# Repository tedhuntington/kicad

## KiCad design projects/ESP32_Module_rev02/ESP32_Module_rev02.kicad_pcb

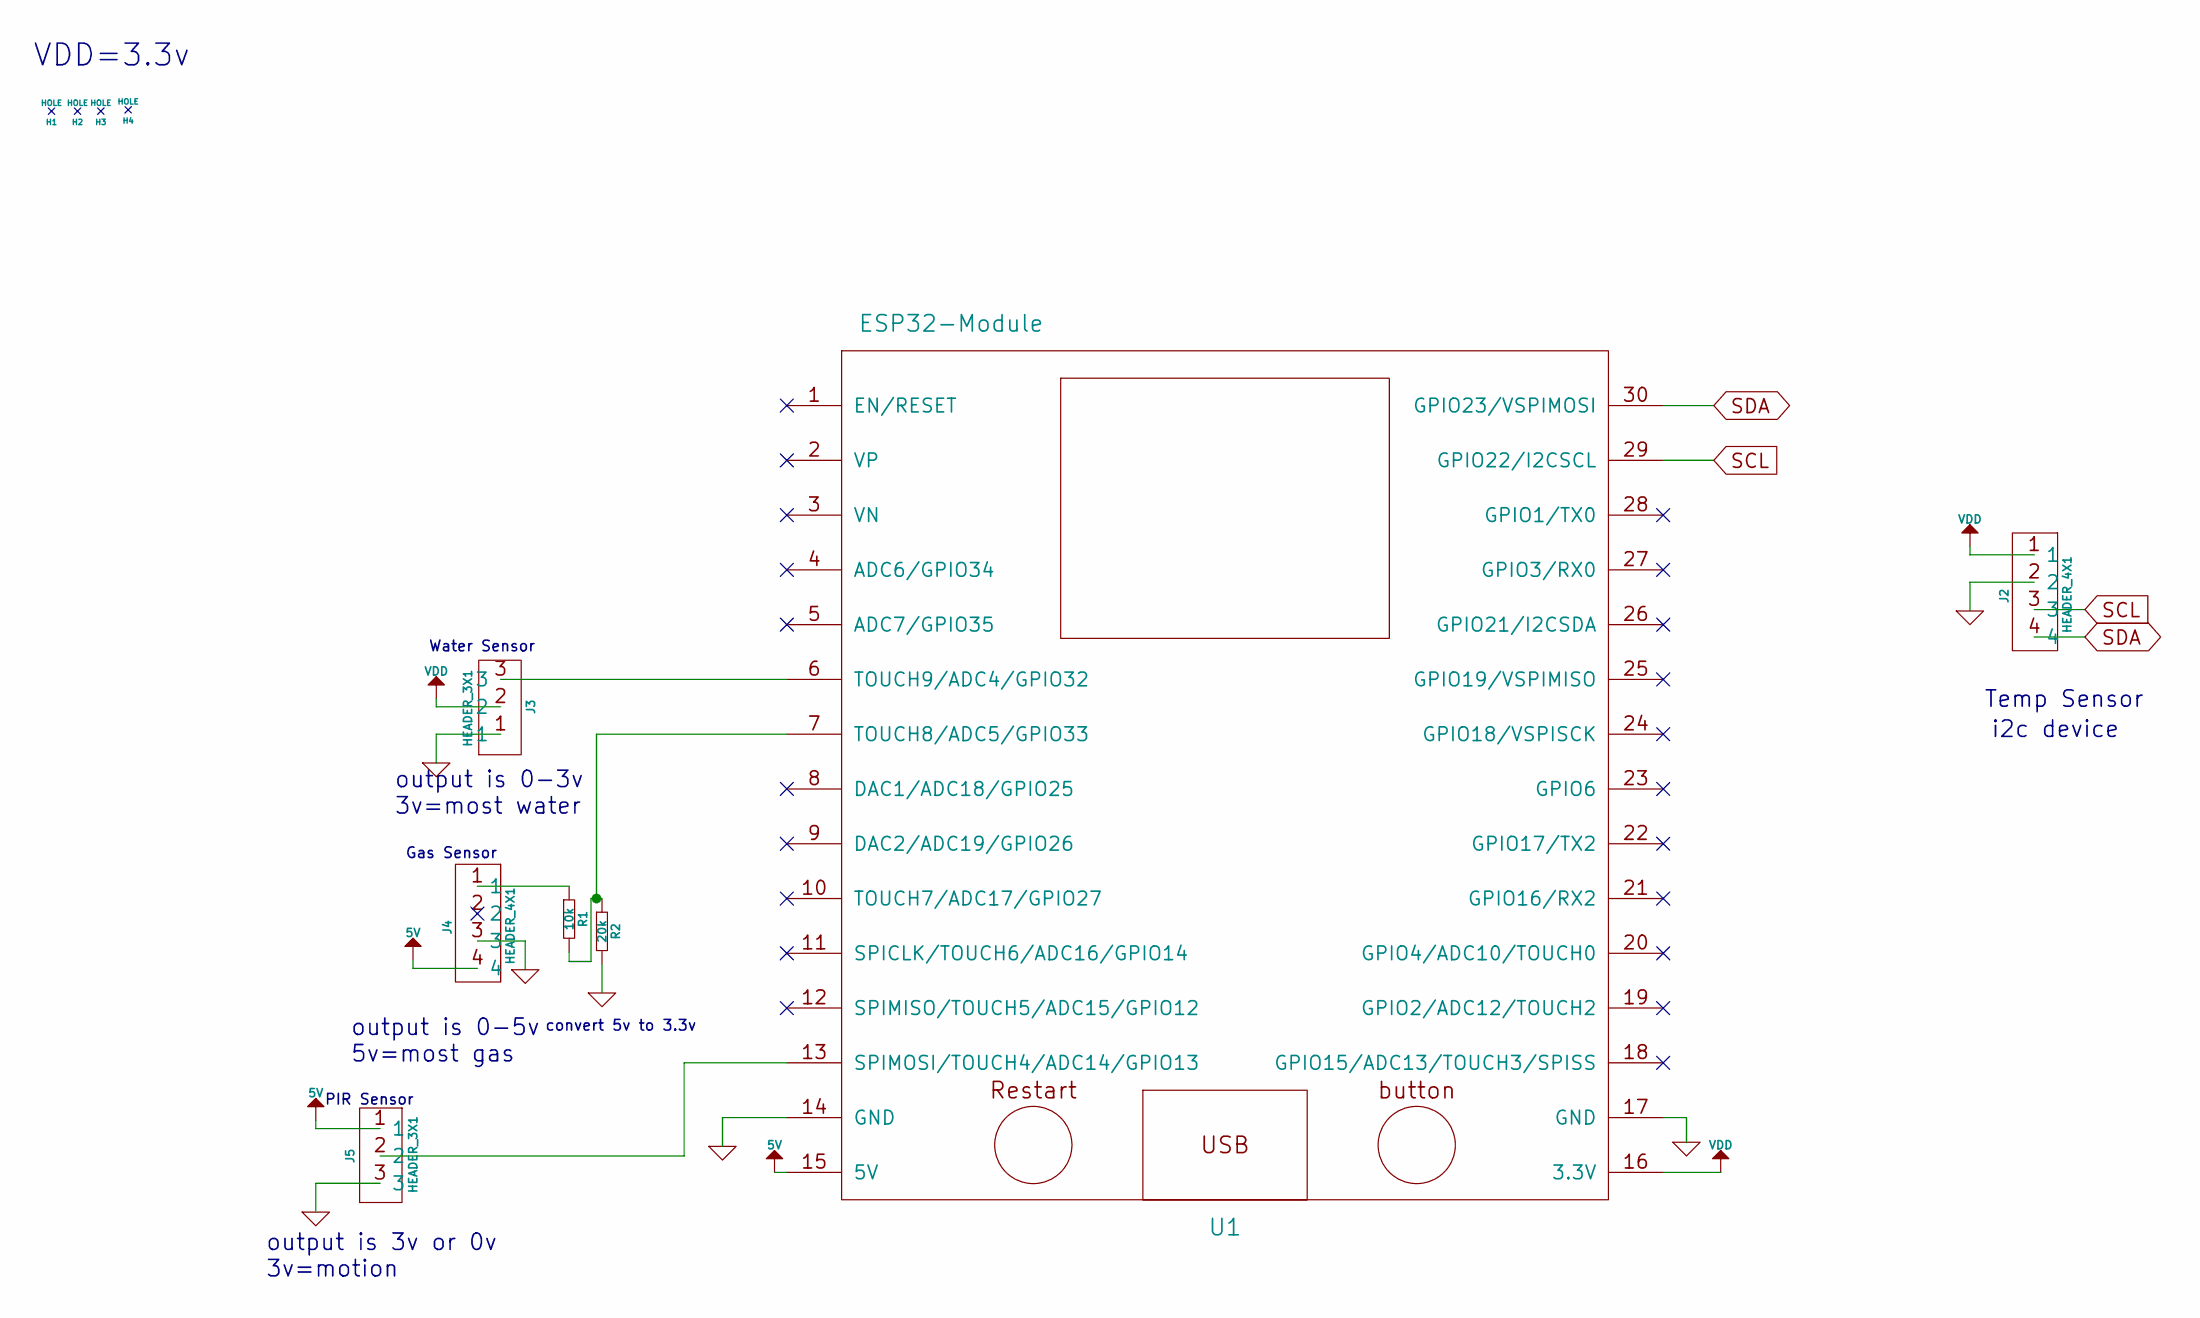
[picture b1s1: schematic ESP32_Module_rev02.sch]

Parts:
H1, H2, H3, H4: HOLE; TED_Hole_3mm
J2, J4: HEADER_4X1; TED_HEADER_4x1
J3, J5: HEADER_3X1; TED_HEADER_3x1
R1: 10k; TED_SM0603_R
R2: 20k; TED_SM0603_R
U1: ESP32-Module; TED_ESP32_Module_30pin

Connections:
5V: J4.4, J5.1, U1.15 (5V)
GND: J2.2, J3.1, J4.3, J5.3, R2.2, U1.14 (GND), U1.17 (GND); also elsewhere on the board
unnamed 2: U1.1 (EN/RESET); also elsewhere on the board
unnamed: J3.3, U1.6 (TOUCH9/ADC4/GPIO32)
unnamed: J4.1, R1.1
unnamed: J5.2, U1.13 (SPIMOSI/TOUCH4/ADC14/GPIO13)
unnamed: R1.2, R2.1, U1.7 (TOUCH8/ADC5/GPIO33)
SCL: J2.3, U1.29 (GPIO22/I2CSCL)
SDA: J2.4, U1.30 (GPIO23/VSPIMOSI)
VDD: J2.1, J3.2, U1.16 (3.3V)

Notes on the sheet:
VDD=3.3v
Water Sensor
PIR Sensor
Temp Sensor
output is 3v or 0v 3v=motion
output is 0-3v 3v=most water
i2c device
Gas Sensor
output is 0-5v 5v=most gas
convert 5v to 3.3v

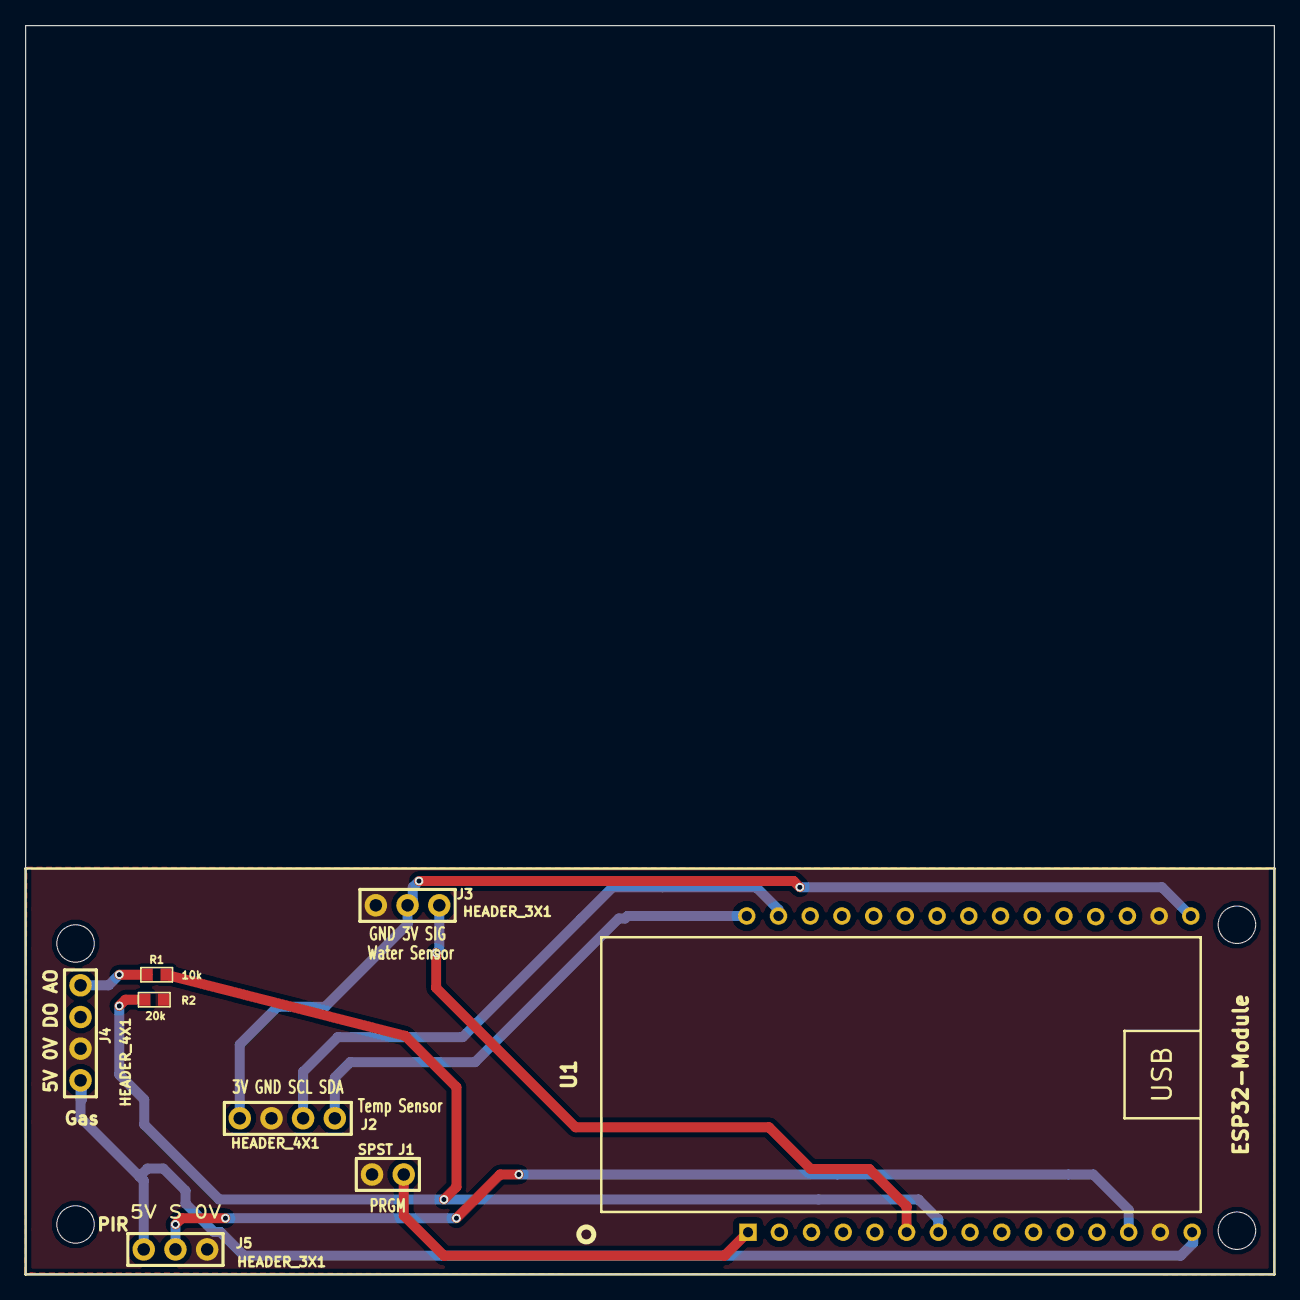
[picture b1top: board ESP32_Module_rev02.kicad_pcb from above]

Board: 2 copper layers, 100.0 x 100.0 mm, 12 parts (0 on the bottom side), 10 nets.

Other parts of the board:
J1: SPST; TED_DIPSWITCH_1

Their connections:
GND: J1.2; also elsewhere on the board
unnamed 2: J1.1; also elsewhere on the board

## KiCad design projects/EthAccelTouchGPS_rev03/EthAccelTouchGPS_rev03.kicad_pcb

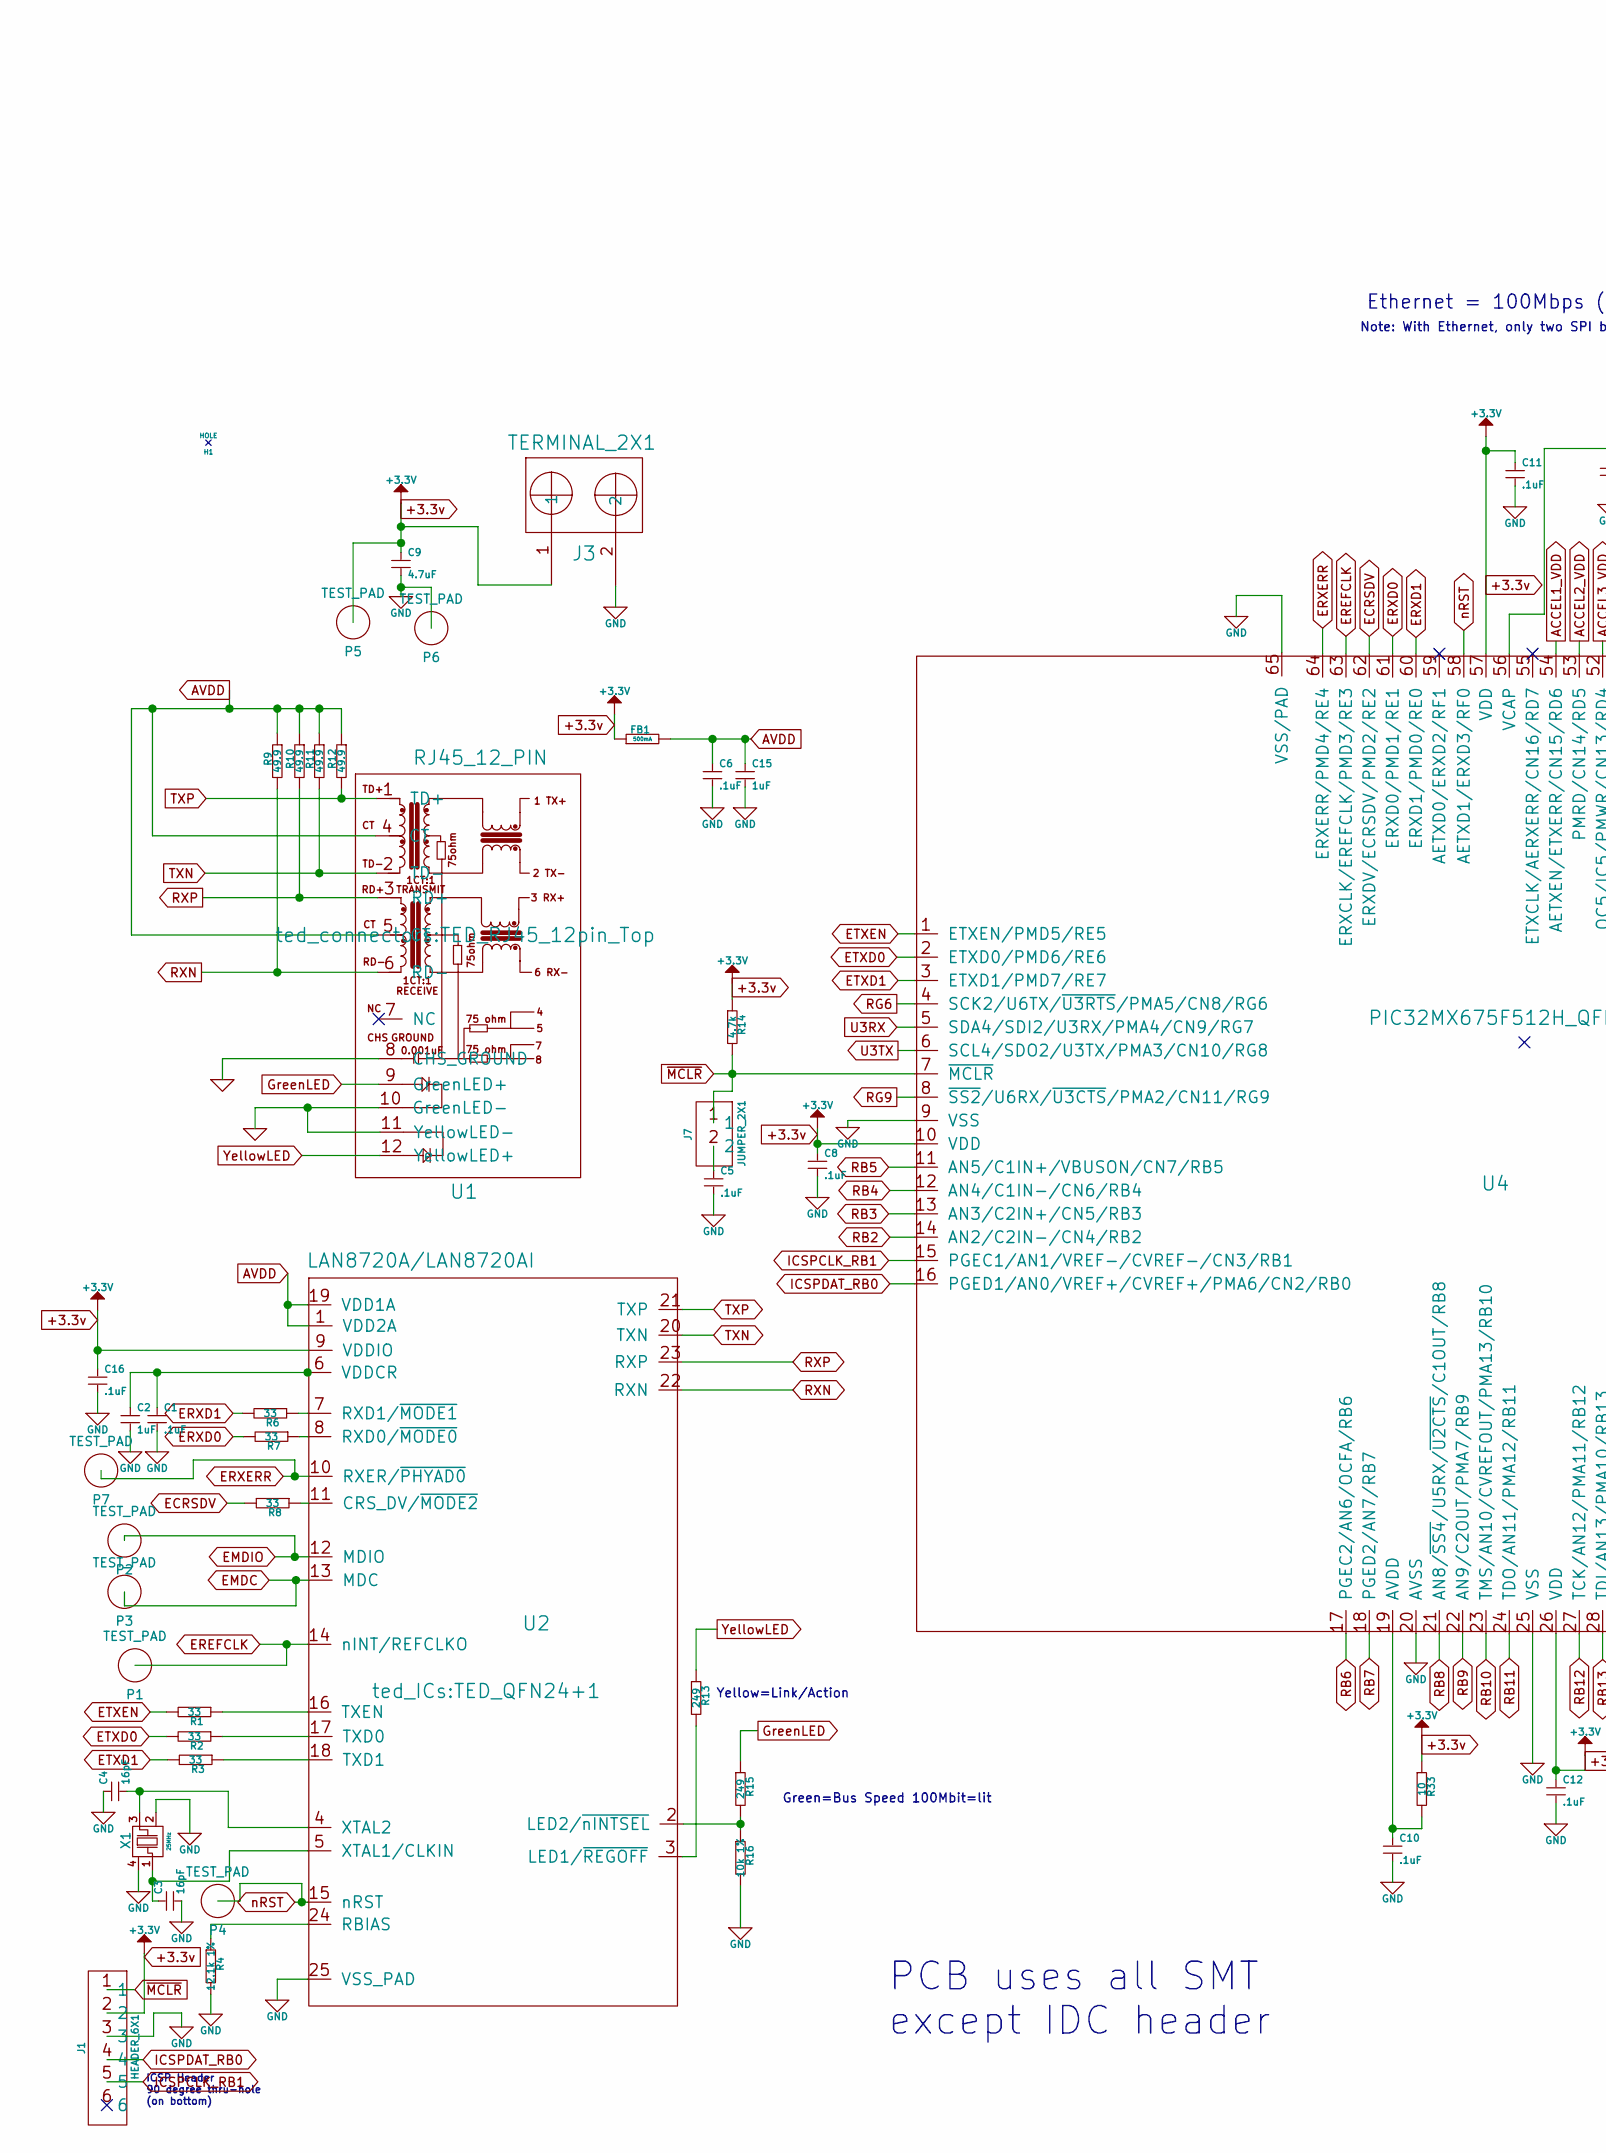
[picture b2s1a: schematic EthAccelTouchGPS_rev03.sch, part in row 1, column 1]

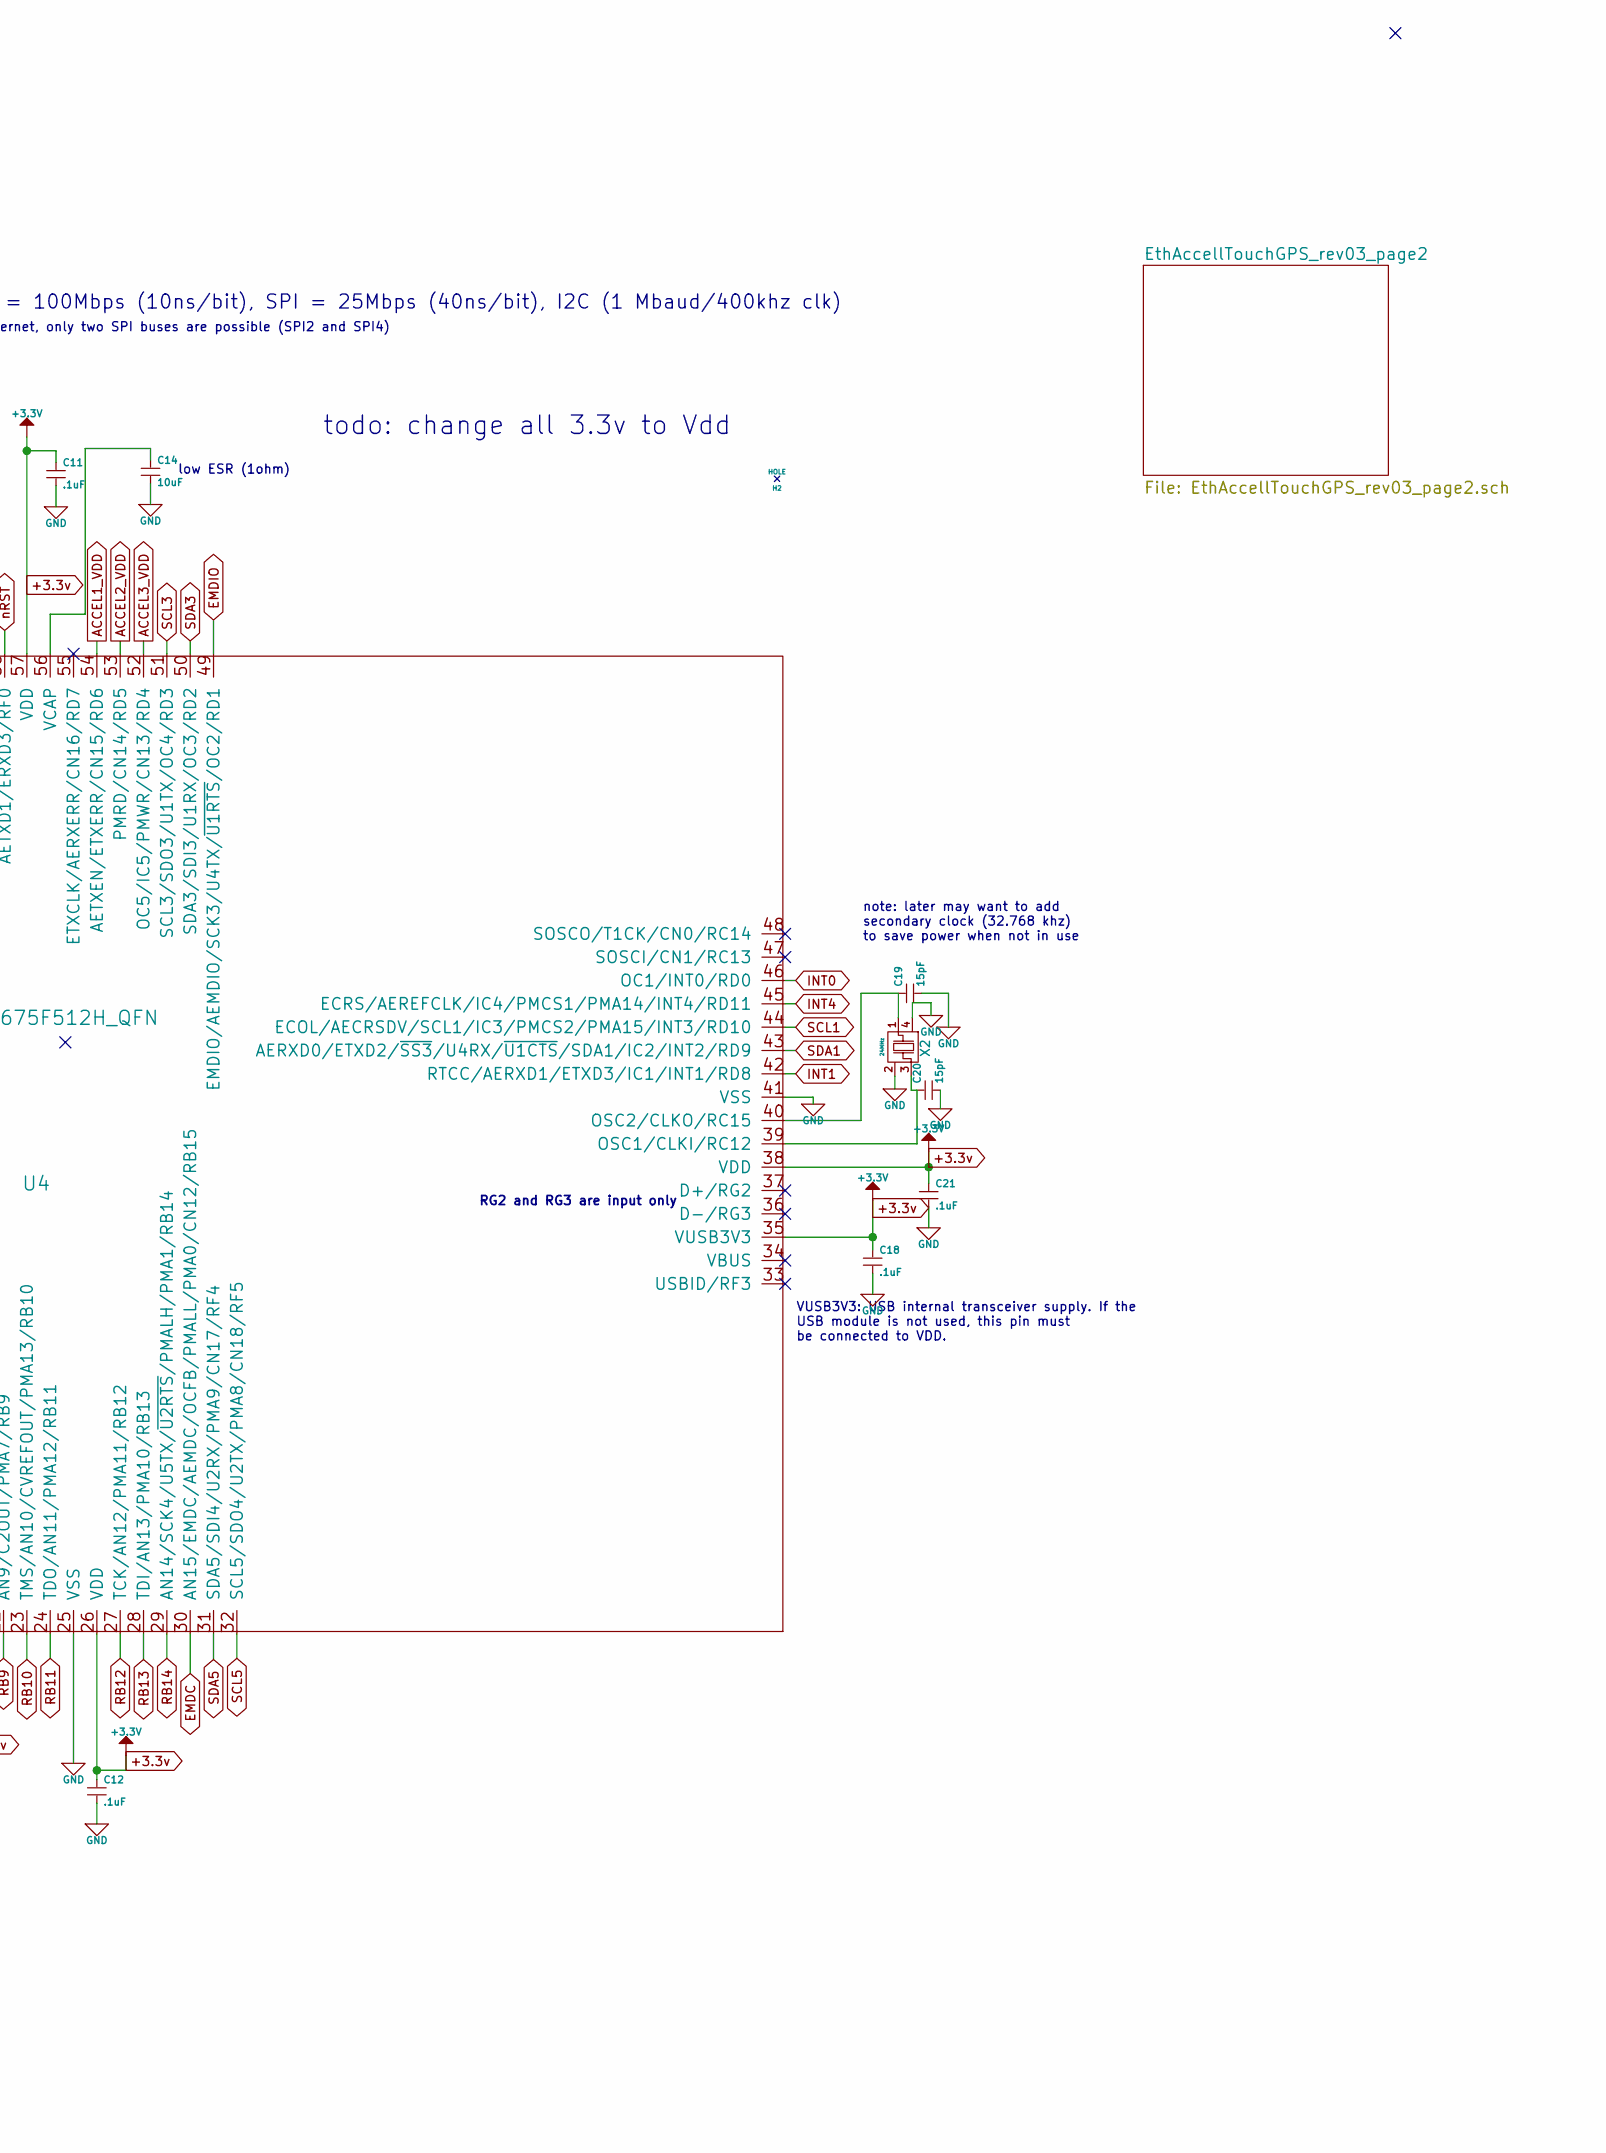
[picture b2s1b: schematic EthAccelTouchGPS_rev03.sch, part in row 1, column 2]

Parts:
C1, C5, C6, C8, C10, C11, C12, C16, C18, C21: .1uF; TED_SM1608_0603_C
C2, C15: 1uF; TED_SM1608_0603_C
C3, C4: 16pF; TED_SM1608_0603_C
C9: 4.7uF; TED_SM1608_0603_C
C14: 10uF; TED_SM2012_0805_C
C19, C20: 15pF; TED_SM1608_0603_C
FB1: 500mA; TED_SM0805_R
H1, H2: HOLE; TED_Hole_3mm
J1: HEADER_6X1; TED_HEADER_6x1
J3: TERMINAL_2X1; TED_TERMINAL_SPRING_2.54MM_2PIN_1989748
J7: JUMPER_2X1; TED_JUMPER_2x1_SMD
P1, P2, P3, P4, P5, P6, P7: TEST_PAD; TED_TEST_PAD
R1, R2, R3, R6, R7, R8: 33; TED_SM0603_R
R4: 12.1k 1%; TED_SM0603_R
R9, R10, R11, R12: 49.9; TED_SM0603_R
R13, R15: 249; TED_SM0603_R
R14: 4.7k; TED_SM0603_R
R16: 10k 1%; TED_SM0603_R
R33: 10; TED_SM0603_R
U1: RJ45_12_PIN; TED_RJ45_12pin_Top
U2: LAN8720A/LAN8720AI; TED_QFN24+1
U4: PIC32MX675F512H_QFN; TED_QFN64+1H
X1: 25MHz; TED_crystal_FA-20H
X2: 24MHz; crystal_TSX3225

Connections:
+3.3v: C8.1, C9.1, C11.1, C12.1, C16.1, C18.1, C21.1, FB1.1, J1.2, J3.1, P5.1, R14.1, R33.1, U2.9 (VDDIO), U4.10 (VDD), U4.26 (VDD), U4.35 (VUSB3V3), U4.38 (VDD), U4.57 (VDD); also elsewhere on the board
ACCEL1_VDD: U4.54 (AETXEN/ETXERR/CN15/RD6); also elsewhere on the board
ACCEL2_VDD: U4.53 (PMRD/CN14/RD5); also elsewhere on the board
ACCEL3_VDD: U4.52 (OC5/IC5/PMWR/CN13/RD4); also elsewhere on the board
AVDD: C6.1, C15.1, FB1.2, R9.1, R10.1, R11.1, R12.1, U1.4 (CT), U1.5 (CT), U2.1 (VDD2A), U2.19 (VDD1A)
ECRSDV: R8.2, U4.62 (ERXDV/ECRSDV/PMD2/RE2)
EMDC: P3.1, U2.13 (MDC), U4.30 (AN15/EMDC/AEMDC/OCFB/PMALL/PMA0/CN12/RB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)
EMDIO: P2.1, U2.12 (MDIO), U4.49 (EMDIO/AEMDIO/SCK3/U4TX/~U1RTS~/OC2/RD1)
EREFCLK: P1.1, U2.14 (nINT/REFCLKO), U4.63 (ERXCLK/EREFCLK/PMD3/RE3)
ERXD0: R7.2, U4.61 (ERXD0/PMD1/RE1)
ERXD1: R6.2, U4.60 (ERXD1/PMD0/RE0)
ERXERR: P7.1, U2.10 (RXER/~PHYAD0~), U4.64 (ERXERR/PMD4/RE4)
ETXD0: R2.2, U4.2 (ETXD0/PMD6/RE6)
ETXD1: R3.2, U4.3 (ETXD1/PMD7/RE7)
ETXEN: R1.2, U4.1 (ETXEN/PMD5/RE5)
GND: C1.2, C2.2, C3.2, C4.1, C5.2, C6.2, C8.2, C9.2, C10.2, C11.2, C12.2, C14.2, C15.2, C16.2, C18.2, C19.2, C20.2, C21.2, J1.3, J3.2, P6.1, R4.2, R16.2, U1.8 (CHS_GROUND), U1.10 (GreenLED-), U1.11 (YellowLED-), U2.25 (VSS_PAD), U4.9 (VSS), U4.20 (AVSS), U4.25 (VSS), U4.41 (VSS), U4.65 (VSS/PAD), X1.2, X1.4, X2.2, X2.4; also elsewhere on the board
GreenLED: R15.1, U1.9 (GreenLED+)
ICSPCLK_RB1: J1.5, U4.15 (PGEC1/AN1/VREF-/CVREF-/CN3/RB1); also elsewhere on the board
ICSPDAT_RB0: J1.4, U4.16 (PGED1/AN0/VREF+/CVREF+/PMA6/CN2/RB0); also elsewhere on the board
INT0: U4.46 (OC1/INT0/RD0); also elsewhere on the board
INT1: U4.42 (RTCC/AERXD1/ETXD3/IC1/INT1/RD8); also elsewhere on the board
INT4: U4.45 (ECRS/AEREFCLK/IC4/PMCS1/PMA14/INT4/RD11); also elsewhere on the board
unnamed: C1.1, C2.1, U2.6 (VDDCR)
unnamed: C3.1, U2.5 (XTAL1/CLKIN), X1.1
unnamed: C4.2, U2.4 (XTAL2), X1.3
unnamed: C5.1, J7.2
unnamed: C10.1, R33.2, U4.19 (AVDD)
unnamed: C14.1, U4.56 (VCAP)
unnamed: C19.1, U4.40 (OSC2/CLKO/RC15), X2.1
unnamed: C20.1, U4.39 (OSC1/CLKI/RC12), X2.3
unnamed: R1.1, U2.16 (TXEN)
unnamed: R2.1, U2.17 (TXD0)
unnamed: R3.1, U2.18 (TXD1)
unnamed: R4.1, U2.24 (RBIAS)
unnamed: R6.1, U2.7 (RXD1/~MODE1~)
unnamed: R7.1, U2.8 (RXD0/~MODE0~)
unnamed: R8.1, U2.11 (CRS_DV/~MODE2~)
unnamed: R13.2, U2.3 (LED1/~REGOFF~)
unnamed: R15.2, R16.1, U2.2 (LED2/~nINTSEL~)
RB2: U4.14 (AN2/C2IN-/CN4/RB2); also elsewhere on the board
RB3: U4.13 (AN3/C2IN+/CN5/RB3); also elsewhere on the board
RB4: U4.12 (AN4/C1IN-/CN6/RB4); also elsewhere on the board
RB5: U4.11 (AN5/C1IN+/VBUSON/CN7/RB5); also elsewhere on the board
RB6: U4.17 (PGEC2/AN6/OCFA/RB6); also elsewhere on the board
RB7: U4.18 (PGED2/AN7/RB7); also elsewhere on the board
RB8: U4.21 (AN8/~SS4~/U5RX/~U2CTS~/C1OUT/RB8); also elsewhere on the board
RB9: U4.22 (AN9/C2OUT/PMA7/RB9); also elsewhere on the board
RB10: U4.23 (TMS/AN10/CVREFOUT/PMA13/RB10); also elsewhere on the board
RB11: U4.24 (TDO/AN11/PMA12/RB11); also elsewhere on the board
RB12: U4.27 (TCK/AN12/PMA11/RB12); also elsewhere on the board
RB13: U4.28 (TDI/AN13/PMA10/RB13); also elsewhere on the board
RB14: U4.29 (AN14/SCK4/U5TX/~U2RTS~/PMALH/PMA1/RB14); also elsewhere on the board
RG6: U4.4 (SCK2/U6TX/~U3RTS~/PMA5/CN8/RG6); also elsewhere on the board
RG9: U4.8 (~SS2~/U6RX/~U3CTS~/PMA2/CN11/RG9); also elsewhere on the board
RXN: R9.2, U1.6 (RD-), U2.22 (RXN)
RXP: R10.2, U1.3 (RD+), U2.23 (RXP)
SCL1: U4.44 (ECOL/AECRSDV/SCL1/IC3/PMCS2/PMA15/INT3/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); also elsewhere on the board
SCL3: U4.51 (SCL3/SDO3/U1TX/OC4/RD3); also elsewhere on the board
SCL5: U4.32 (SCL5/SDO4/U2TX/PMA8/CN18/RF5); also elsewhere on the board
SDA1: U4.43 (AERXD0/ETXD2/~SS3~/U4RX/~U1CTS~/SDA1/IC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); also elsewhere on the board
SDA3: U4.50 (SDA3/SDI3/U1RX/OC3/RD2); also elsewhere on the board
SDA5: U4.31 (SDA5/SDI4/U2RX/PMA9/CN17/RF4); also elsewhere on the board
TXN: R11.2, U1.2 (TD-), U2.20 (TXN)
TXP: R12.2, U1.1 (TD+), U2.21 (TXP)
U3RX: U4.5 (SDA4/SDI2/U3RX/PMA4/CN9/RG7); also elsewhere on the board
U3TX: U4.6 (SCL4/SDO2/U3TX/PMA3/CN10/RG8); also elsewhere on the board
YellowLED: R13.1, U1.12 (YellowLED+)
nRST: P4.1, U2.15 (nRST), U4.58 (AETXD1/ERXD3/RF0)
~MCLR~: J1.1, J7.1, R14.2, U4.7 (~MCLR~)

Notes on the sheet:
Ethernet = 100Mbps (10ns/bit), SPI = 25Mbps (40ns/bit), I2C (1 Mbaud/400khz clk)
ICSP Header 90 degree thru-hole (on bottom)
PCB uses all SMT except IDC header
Note: With Ethernet, only two SPI buses are possible (SPI2 and SPI4)
note: later may want to add secondary clock (32.768 khz) to save power when not in use
VUSB3V3: USB internal transceiver supply. If the USB module is not used, this pin must be connected to VDD.
Yellow=Link/Action
Green=Bus Speed 100Mbit=lit
todo: change all 3.3v to Vdd
low ESR (1ohm)
RG2 and RG3 are input only

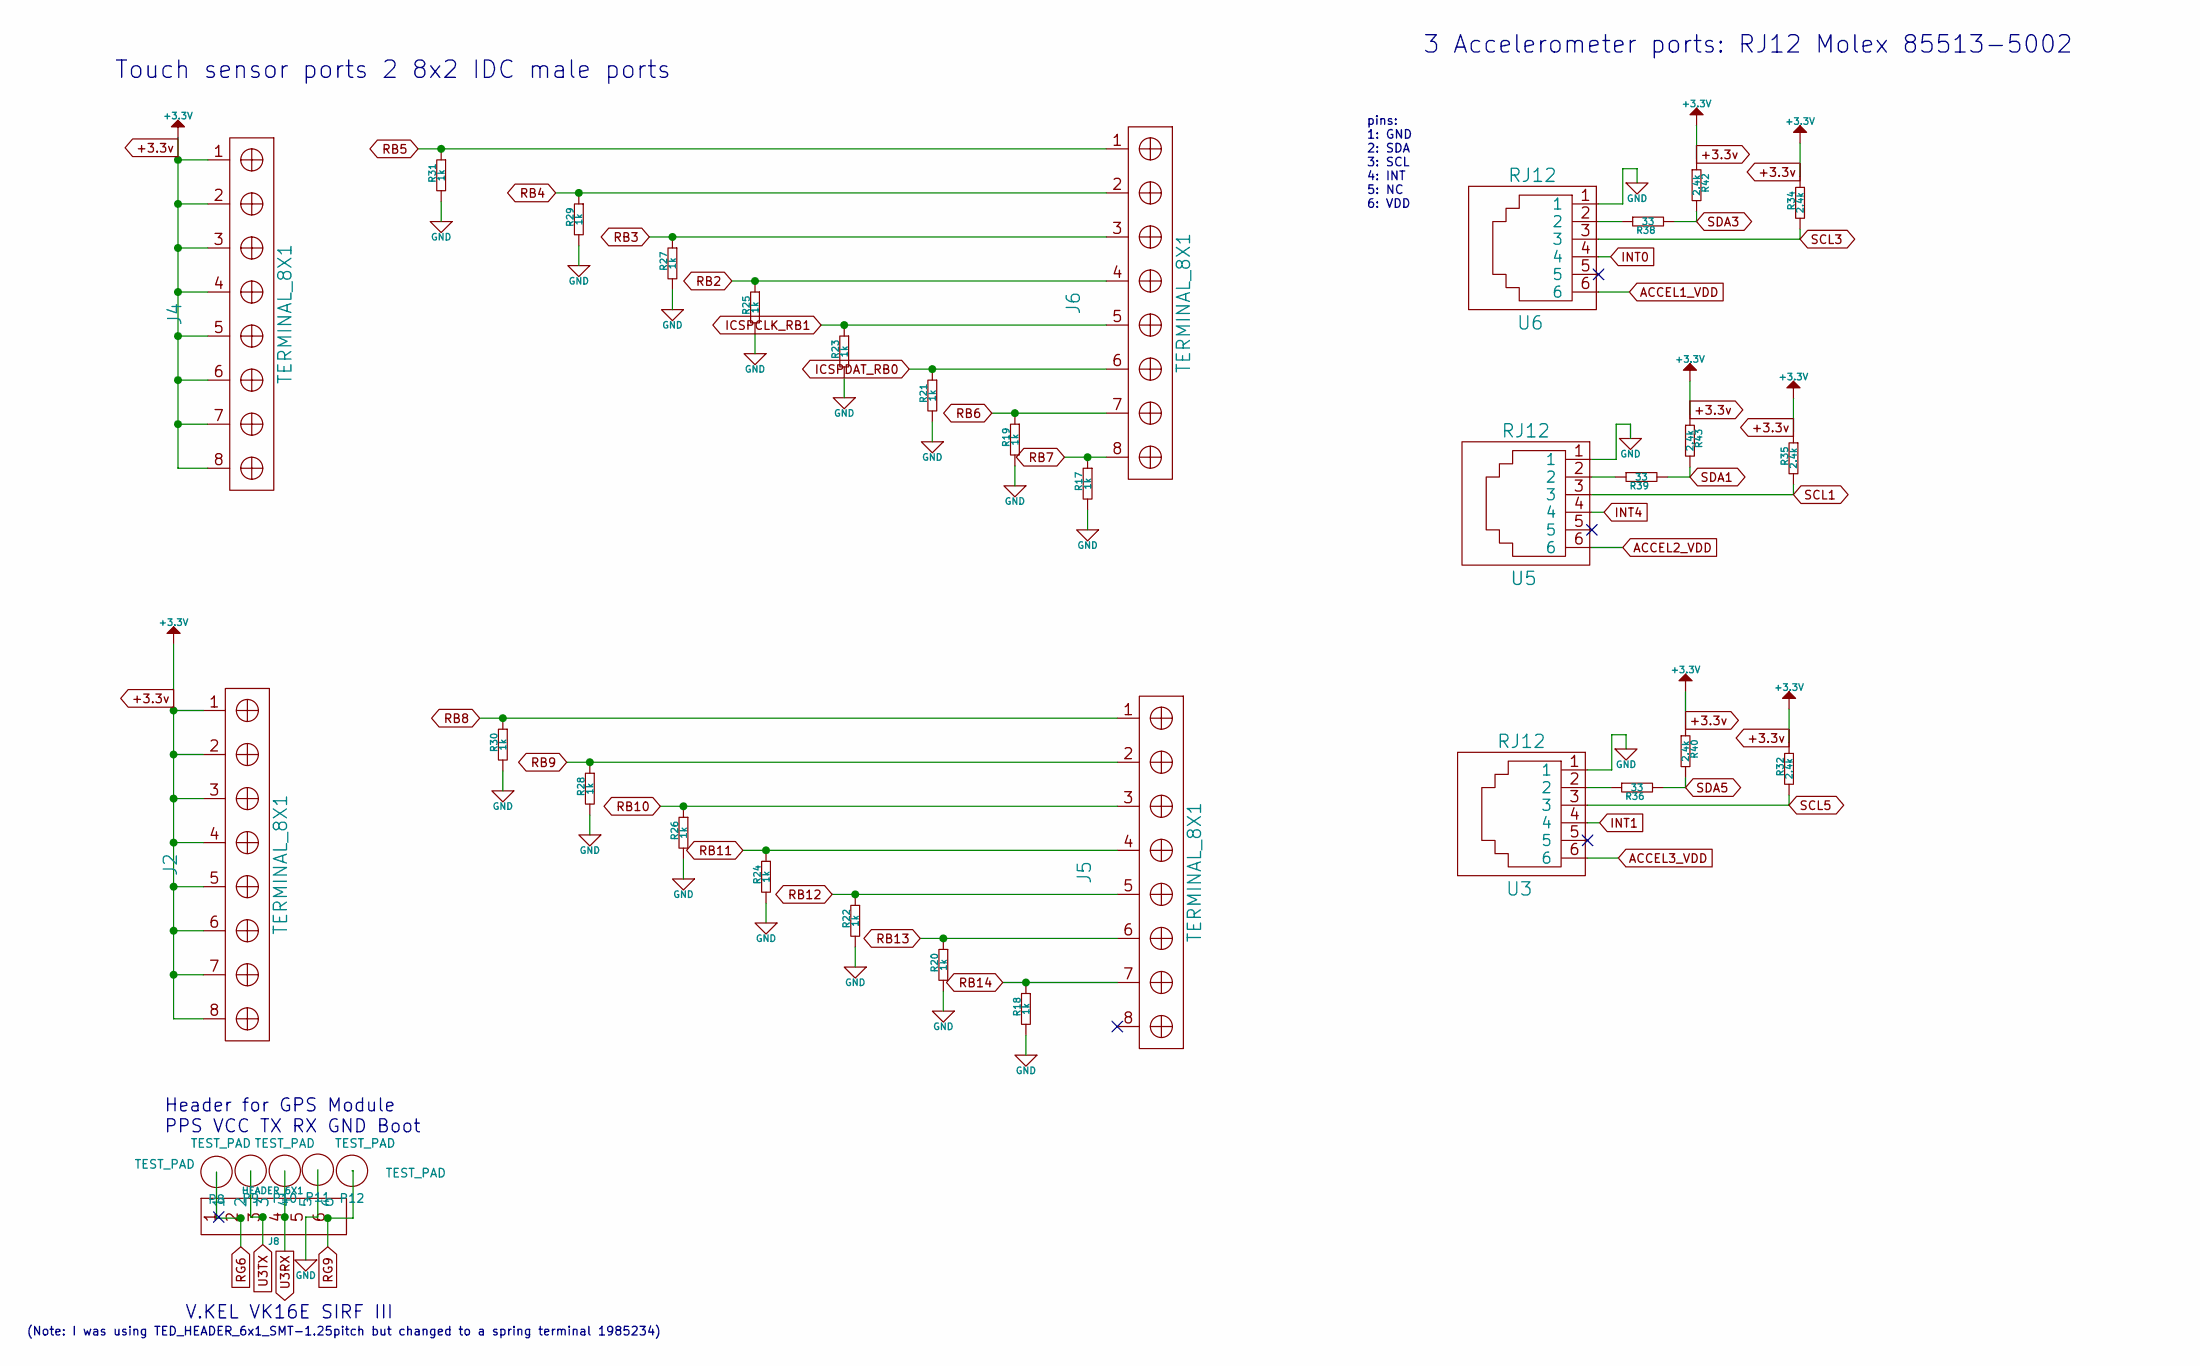
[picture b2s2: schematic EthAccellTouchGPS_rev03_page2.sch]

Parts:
J2, J4, J5, J6: TERMINAL_8X1; TED_Terminal_8x1_1814760
J8: HEADER_6X1; TED_TERMINAL_SPRING_2.54MM_6PIN_1985234
P8, P9, P10, P11, P12: TEST_PAD; TED_TEST_PAD
R17, R18, R19, R20, R21, R22, R23, R24, R25, R26, R27, R28, R29, R30, R31: 1k; TED_SM0603_R
R32, R34, R35, R40, R42, R43: 2.4k; TED_SM0603_R
R36, R38, R39: 33; TED_SM0603_R
U3, U5, U6: RJ12; TED_RJ12_855135002

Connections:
+3.3v: J2.1, J2.2, J2.3, J2.4, J2.5, J2.6, J2.7, J2.8, J4.1, J4.2, J4.3, J4.4, J4.5, J4.6, J4.7, J4.8, R32.1, R34.1, R35.1, R40.1, R42.1, R43.1; also elsewhere on the board
ACCEL1_VDD: U6.6; also elsewhere on the board
ACCEL2_VDD: U5.6; also elsewhere on the board
ACCEL3_VDD: U3.6; also elsewhere on the board
GND: J8.5, P11.1, R17.2, R18.2, R19.2, R20.2, R21.2, R22.2, R23.2, R24.2, R25.2, R26.2, R27.2, R28.2, R29.2, R30.2, R31.2, U3.1, U5.1, U6.1; also elsewhere on the board
ICSPCLK_RB1: J6.5, R23.1; also elsewhere on the board
ICSPDAT_RB0: J6.6, R21.1; also elsewhere on the board
INT0: U6.4; also elsewhere on the board
INT1: U3.4; also elsewhere on the board
INT4: U5.4; also elsewhere on the board
unnamed: R36.1, U3.2
unnamed: R38.1, U6.2
unnamed: R39.1, U5.2
RB2: J6.4, R25.1; also elsewhere on the board
RB3: J6.3, R27.1; also elsewhere on the board
RB4: J6.2, R29.1; also elsewhere on the board
RB5: J6.1, R31.1; also elsewhere on the board
RB6: J6.7, R19.1; also elsewhere on the board
RB7: J6.8, R17.1; also elsewhere on the board
RB8: J5.1, R30.1; also elsewhere on the board
RB9: J5.2, R28.1; also elsewhere on the board
RB10: J5.3, R26.1; also elsewhere on the board
RB11: J5.4, R24.1; also elsewhere on the board
RB12: J5.5, R22.1; also elsewhere on the board
RB13: J5.6, R20.1; also elsewhere on the board
RB14: J5.7, R18.1; also elsewhere on the board
RG6: J8.2, P8.1; also elsewhere on the board
RG9: J8.6, P12.1; also elsewhere on the board
SCL1: R35.2, U5.3; also elsewhere on the board
SCL3: R34.2, U6.3; also elsewhere on the board
SCL5: R32.2, U3.3; also elsewhere on the board
SDA1: R39.2, R43.2; also elsewhere on the board
SDA3: R38.2, R42.2; also elsewhere on the board
SDA5: R36.2, R40.2; also elsewhere on the board
U3RX: J8.4, P10.1; also elsewhere on the board
U3TX: J8.3, P9.1; also elsewhere on the board

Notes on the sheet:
Touch sensor ports 2 8x2 IDC male ports
3 Accelerometer ports: RJ12 Molex 85513-5002
pins: 1: GND 2: SDA 3: SCL 4: INT 5: NC 6: VDD
Header for GPS Module PPS VCC TX RX GND Boot
V.KEL VK16E SIRF III
(Note: I was using TED_HEADER_6x1_SMT-1.25pitch but changed to a spring terminal 1985234)
